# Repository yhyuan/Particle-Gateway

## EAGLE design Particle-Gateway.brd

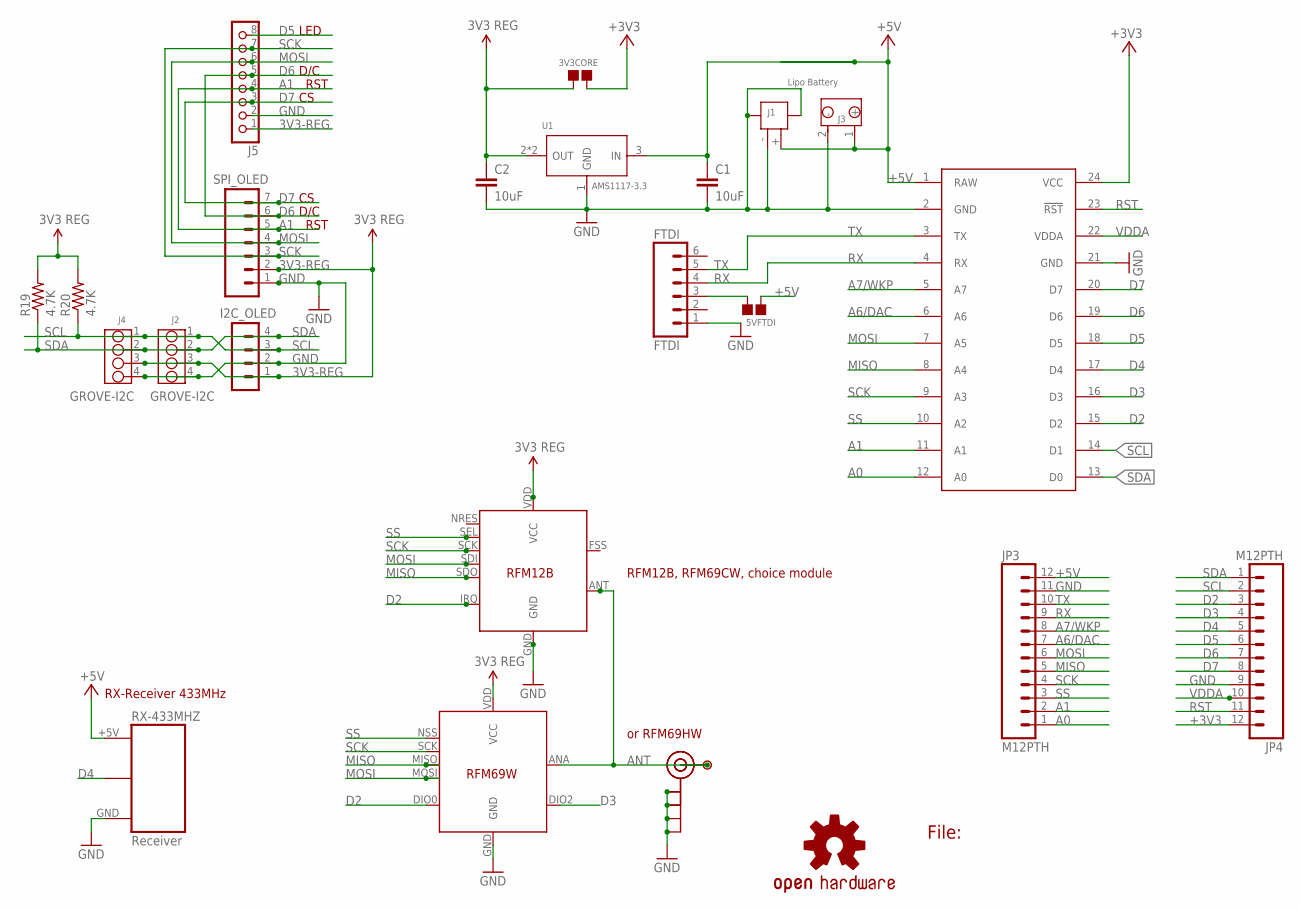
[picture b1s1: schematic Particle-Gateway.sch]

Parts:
3V3CORE, 5VFTDI: PAD-JUMPER-2P; 2P-SMD-1.78X1.27
C1, C2: 10uF; 0805-CAP
FTDI: FTDI; 1X06
I2C_OLED: CON_HEADER_1X04'SMALL''; M1X4
J1: JST-2P-SMD'2.0'; 2P-SMD-2.0-90D
J2: GROVE-I2C; 4P-2.0-90D
J3: Lipo Battery; 2P-2.0-90D
J4: GROVE-I2C; 4P-2.0
J5: CON_HEADER_1X08-PTH; M1X8
J$1: SMA_EDGE; SMA-EDGE
JP3, JP4: M12PTH; 1X12-SMALL-PADS
LOGO2: OSHW-LOGOL; OSHW-LOGO-L
P1: PADSMALL; PAD-SMALL
R19, R20: 4.7K; 0805-RES
RX-433MHZ: Receiver; RF-LINK_RX_NO_SILK
SPARKCORE: SPARK_CORECORE; SPARK_CORE
SPI_OLED: CON_HEADER_1X07'SMALL'; M1X7
U1: AMS1117-3.3; SOT223
U$2: RFM12B; RFM12B-MINPADS
U$3: RFM69W; RFM69W-MINPADS
U-FL: U.FL

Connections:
3V3-REG: 3V3CORE.1, C2.1, I2C_OLED.1, J2.3, J4.3, J5.1, R19.2, R20.2, SPI_OLED.2, U1.2 (OUT), U1.TER (OUT), U$2.VDD (VCC), U$3.VDD (VCC)
+3V3: 3V3CORE.2, JP4.12, SPARKCORE.24 (VCC)
+5V: 5VFTDI.1, C1.1, J1.+ (1), J3.1 (+), JP3.12, RX-433MHZ.+5V, SPARKCORE.1 (RAW), U1.3 (IN)
A0: JP3.1, SPARKCORE.12 (A0)
A1: J5.4, JP3.2, SPARKCORE.11 (A1), SPI_OLED.5
A6/DAC: JP3.7, SPARKCORE.6 (A6)
A7/WKP: JP3.8, SPARKCORE.5 (A7)
ANT: J$1.SIG (SIGNAL), P1.1, U$2.ANT, U$3.ANA (ANT), U-FL.3 (SIGNAL)
D2: JP4.3, SPARKCORE.15 (D2), U$2.IRQ, U$3.DIO0
D3: JP4.4, SPARKCORE.16 (D3), U$3.DIO2
D4: JP4.5, RX-433MHZ.DATA@1 (DATA), RX-433MHZ.DATA@2 (DATA), SPARKCORE.17 (D4)
D5: J5.8, JP4.6, SPARKCORE.18 (D5)
D6: J5.5, JP4.7, SPARKCORE.19 (D6), SPI_OLED.6
D7: J5.3, JP4.8, SPARKCORE.20 (D7), SPI_OLED.7
GND: C1.2, C2.2, FTDI.1, I2C_OLED.2, J1.3, J1.4, J1.- (2), J2.4, J3.2 (-), J4.4, J5.2, J$1.GND@0 (GND), J$1.GND@1 (GND), J$1.GND@2 (GND), J$1.GND@3 (GND), JP3.11, JP4.9, RX-433MHZ.GND, SPARKCORE.2 (GND), SPARKCORE.21 (GND), SPI_OLED.1, U1.1 (GND), U$2.GND, U$3.GND, U-FL.1 (GND), U-FL.2 (GND)
MISO: JP3.5, SPARKCORE.8 (A4), U$2.SDO, U$3.MISO
MOSI: J5.6, JP3.6, SPARKCORE.7 (A5), SPI_OLED.4, U$2.SDI, U$3.MOSI
unnamed: 5VFTDI.2, FTDI.3
RST: JP4.11, SPARKCORE.23 (!RST)
RX: FTDI.4, JP3.9, SPARKCORE.4 (RX)
SCK: J5.7, JP3.4, SPARKCORE.9 (A3), SPI_OLED.3, U$2.SCK, U$3.SCK
SCL: I2C_OLED.3, J2.1, J4.1, JP4.2, R20.1, SPARKCORE.14 (D1)
SDA: I2C_OLED.4, J2.2, J4.2, JP4.1, R19.1, SPARKCORE.13 (D0)
SS: JP3.3, SPARKCORE.10 (A2), U$2.SEL, U$3.NSS (SEL)
TX: FTDI.5, JP3.10, SPARKCORE.3 (TX)
VDDA: JP4.10, SPARKCORE.22 (VDDA)

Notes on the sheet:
RFM12B, RFM69CW, choice module
or RFM69HW
RX-Receiver 433MHz
D/C
LED
RST
File:

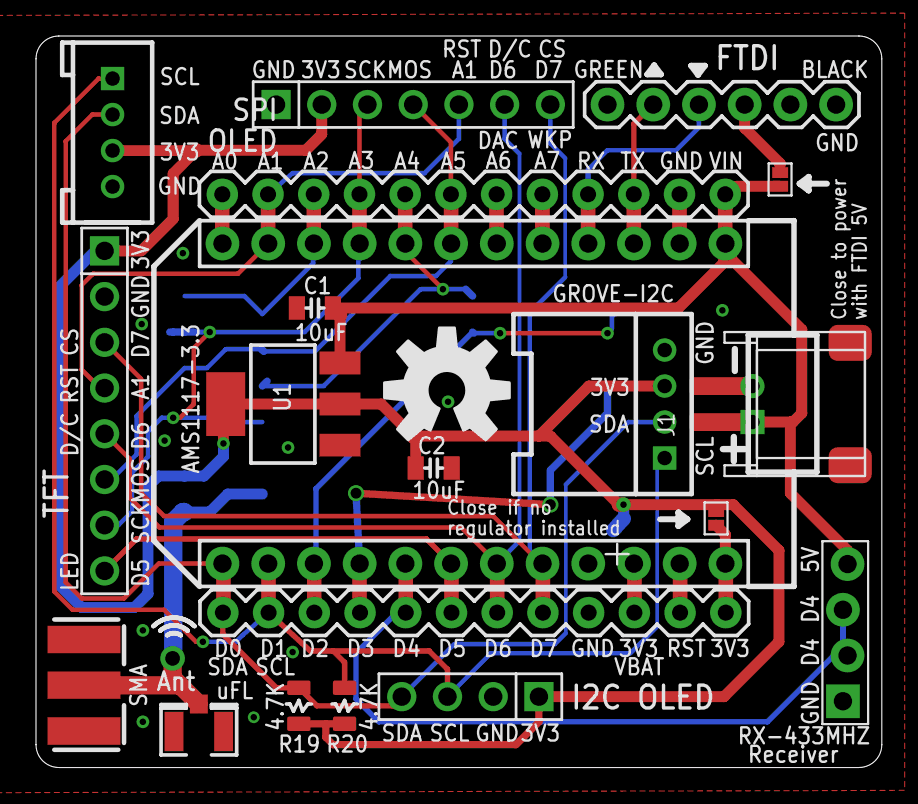
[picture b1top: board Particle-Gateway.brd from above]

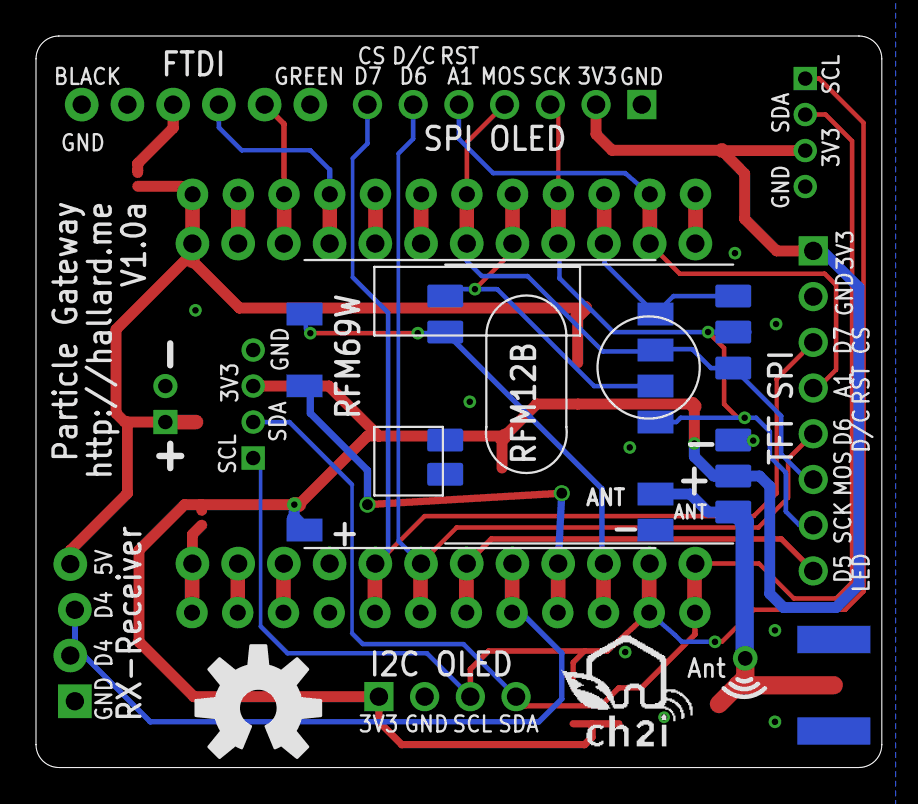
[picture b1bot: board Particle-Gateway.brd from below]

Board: 2 copper layers, 47.0 x 40.6 mm, 27 parts (4 on the bottom side), 26 nets.

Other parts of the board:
LOGO1: OSHW-LOGOL; OSHW-LOGO-L
U$1: LOGO_CH2I_75MM

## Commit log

2015-11-13 Connect DIO2 to D3

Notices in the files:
parts and their libraries:
microbuilder: This work is placed in the public domain, and may be freely used for commercial and non-commercial work with the following conditions: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
SparkFun-Aesthetics: Licensing: Creative Commons ShareAlike 4.0 International - https://creativecommons.org/licenses/by-sa/4.0
